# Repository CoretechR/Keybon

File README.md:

# Keybon - Adaptive Macro Keyboard

Keybon is a macro keyboard with configurable layouts and functions. Integrated into each of its nine tactile buttons is a 0.66” OLED screen. Depending on which app is active on the connected computer, Keybon switches to the suitable key layout thanks to its companion software.

# Instructions

1.  Download the USB bootloader: https://github.com/rogerclarkmelbourne/STM32duino-bootloader

    Connect a USB-to-Serial adapter to the TX/RX pins of your board. Close the BOOT0 jumper before applying power.
    
    Flash the USB bootloader to the STM32 via the STM32 flasher:  https://www.st.com/en/development-tools/flasher-stm32.html
2.  Install the required Arduino libraries listed in the keybon.ino file

    Important: Adafruit_GFX_Library version 1.7.5 must be installed (dependencies for newer versions are incompatible with the STM32)
    
    Add the following lines to the Adafruit_SSD1306 library (in Arduino\libraries\Adafruit_SSD1306\Adafruit_SSD1306.cpp) 
    
    ```C++
    else if ((WIDTH == 128) && (HEIGHT == 48)) {
    comPins = 0x12;
	  contrast = (vccstate == SSD1306_EXTERNALVCC) ? 0x9F : 0xCF;
    }
    ```
3.  Install STM32 support for the Arduino IDE: https://github.com/rogerclarkmelbourne/Arduino_STM32

    Install the corresponding drivers: https://github.com/rogerclarkmelbourne/Arduino_STM32/tree/master/drivers
4.  Compile and upload the Arduino sketch:

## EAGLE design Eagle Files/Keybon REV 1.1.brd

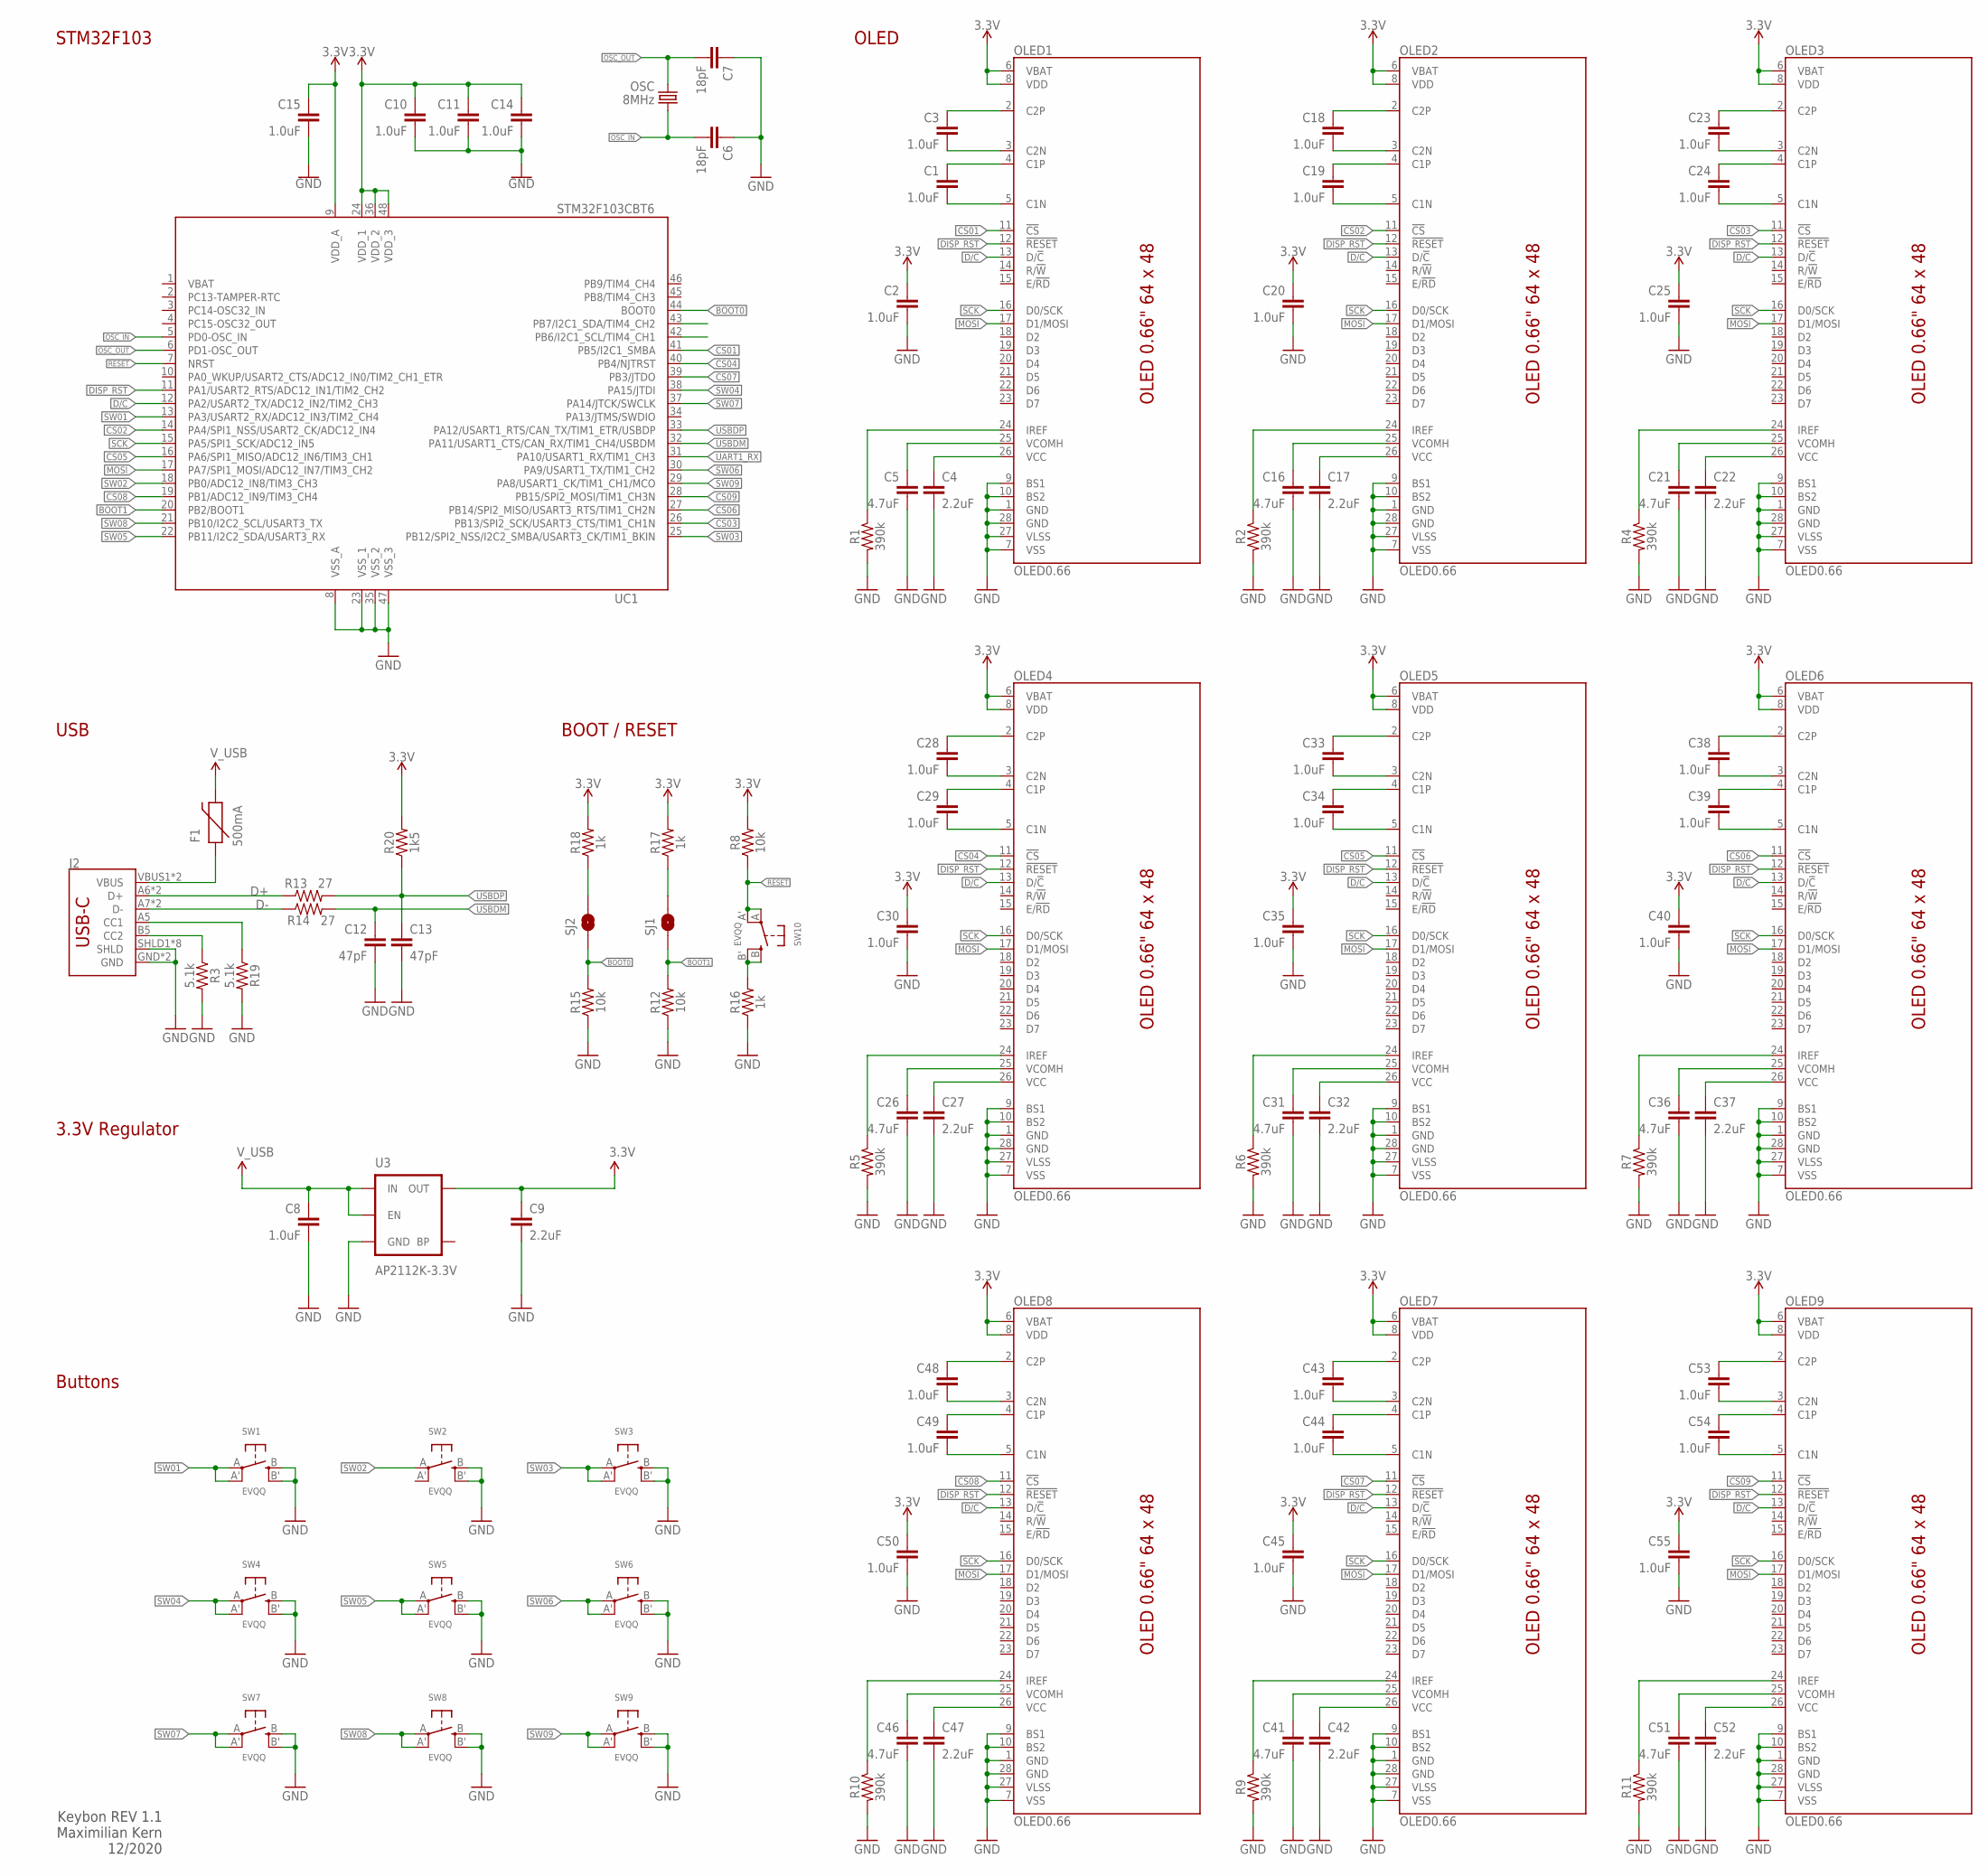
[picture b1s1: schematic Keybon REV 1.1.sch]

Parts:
C1, C2, C3, C8, C10, C11, C14, C15, C18, C19, C20, C23, C24, C25, C28, C29, C30, C33, C34, C35, C38, C39, C40, C43, C44, C45, C48, C49, C50, C53, C54, C55: 1.0uF; 0805
C4, C9, C17, C22, C27, C32, C37, C42, C47, C52: 2.2uF; 0805
C5, C16, C21, C26, C31, C36, C41, C46, C51: 4.7uF; 0603
C6, C7: 18pF; 0603
C12, C13: 47pF; 0603
F1: 500mA; PTC-1206
J2: USB_C16PIN; USB-C-16P
OLED1, OLED2, OLED3, OLED4, OLED5, OLED6, OLED7, OLED8, OLED9: OLED0.66; OLED-0.66-64X48
OSC: 8MHz; CRYSTAL-SMD-5X3
R1, R2, R4, R5, R6, R7, R9, R10, R11: 390k; 0603
R3, R19: 5.1k; 0603
R8, R12, R15: 10k; 0603
R13, R14: 27; 0603
R16, R17, R18: 1k; 0603
R20: 1k5; 0603
SJ1, SJ2: JUMPER-PAD-2-NOYES_SILK; PAD-JUMPER-2-NO_YES_SILK
SW1, SW2, SW3, SW4, SW5, SW6, SW7, SW8, SW9, SW10: EVQQ; EVQ-Q2_SMALLER
U3: AP2112K-3.3V; SOT23-5
UC1: STM32F103CBT6; LQFP48

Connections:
3.3V: C2.1, C9.1, C10.1, C11.1, C14.1, C15.1, C20.1, C25.1, C30.1, C35.1, C40.1, C45.1, C50.1, C55.1, OLED1.6 (VBAT), OLED1.8 (VDD), OLED2.6 (VBAT), OLED2.8 (VDD), OLED3.6 (VBAT), OLED3.8 (VDD), OLED4.6 (VBAT), OLED4.8 (VDD), OLED5.6 (VBAT), OLED5.8 (VDD), OLED6.6 (VBAT), OLED6.8 (VDD), OLED7.6 (VBAT), OLED7.8 (VDD), OLED8.6 (VBAT), OLED8.8 (VDD), OLED9.6 (VBAT), OLED9.8 (VDD), R8.2, R17.2, R18.2, R20.2, U3.5 (OUT), UC1.9 (VDD_A), UC1.24 (VDD_1), UC1.36 (VDD_2), UC1.48 (VDD_3)
BOOT0: R15.2, SJ2.1, UC1.44 (BOOT0)
BOOT1: R12.2, SJ1.1, UC1.20 (PB2/BOOT1)
C1N: C1.2, OLED1.5 (C1N)
C1N1: C19.2, OLED2.5 (C1N)
C1N2: C24.2, OLED3.5 (C1N)
C1N3: C29.2, OLED4.5 (C1N)
C1N4: C34.2, OLED5.5 (C1N)
C1N5: C39.2, OLED6.5 (C1N)
C1N6: C44.2, OLED7.5 (C1N)
C1N7: C49.2, OLED8.5 (C1N)
C1N8: C54.2, OLED9.5 (C1N)
C1P: C1.1, OLED1.4 (C1P)
C1P1: C19.1, OLED2.4 (C1P)
C1P2: C24.1, OLED3.4 (C1P)
C1P3: C29.1, OLED4.4 (C1P)
C1P4: C34.1, OLED5.4 (C1P)
C1P5: C39.1, OLED6.4 (C1P)
C1P6: C44.1, OLED7.4 (C1P)
C1P7: C49.1, OLED8.4 (C1P)
C1P8: C54.1, OLED9.4 (C1P)
C2N: C3.2, OLED1.3 (C2N)
C2N1: C18.2, OLED2.3 (C2N)
C2N2: C23.2, OLED3.3 (C2N)
C2N3: C28.2, OLED4.3 (C2N)
C2N4: C33.2, OLED5.3 (C2N)
C2N5: C38.2, OLED6.3 (C2N)
C2N6: C43.2, OLED7.3 (C2N)
C2N7: C48.2, OLED8.3 (C2N)
C2N8: C53.2, OLED9.3 (C2N)
C2P: C3.1, OLED1.2 (C2P)
C2P1: C18.1, OLED2.2 (C2P)
C2P2: C23.1, OLED3.2 (C2P)
C2P3: C28.1, OLED4.2 (C2P)
C2P4: C33.1, OLED5.2 (C2P)
C2P5: C38.1, OLED6.2 (C2P)
C2P6: C43.1, OLED7.2 (C2P)
C2P7: C48.1, OLED8.2 (C2P)
C2P8: C53.1, OLED9.2 (C2P)
CS01: OLED1.11 (!CS!), UC1.41 (PB5/I2C1_SMBA)
CS02: OLED2.11 (!CS!), UC1.14 (PA4/SPI1_NSS/USART2_CK/ADC12_IN4)
CS03: OLED3.11 (!CS!), UC1.26 (PB13/SPI2_SCK/USART3_CTS/TIM1_CH1N)
CS04: OLED4.11 (!CS!), UC1.40 (PB4/NJTRST)
CS05: OLED5.11 (!CS!), UC1.16 (PA6/SPI1_MISO/ADC12_IN6/TIM3_CH1)
CS06: OLED6.11 (!CS!), UC1.27 (PB14/SPI2_MISO/USART3_RTS/TIM1_CH2N)
CS07: OLED7.11 (!CS!), UC1.39 (PB3/JTDO)
CS08: OLED8.11 (!CS!), UC1.19 (PB1/ADC12_IN9/TIM3_CH4)
CS09: OLED9.11 (!CS!), UC1.28 (PB15/SPI2_MOSI/TIM1_CH3N)
D+: J2.A6 (D+), J2.B6 (D+), R13.1
D-: J2.A7 (D-), J2.B7 (D-), R14.1
D/C: OLED1.13 (D/!C!), OLED2.13 (D/!C!), OLED3.13 (D/!C!), OLED4.13 (D/!C!), OLED5.13 (D/!C!), OLED6.13 (D/!C!), OLED7.13 (D/!C!), OLED8.13 (D/!C!), OLED9.13 (D/!C!), UC1.12 (PA2/USART2_TX/ADC12_IN2/TIM2_CH3)
DISP_RST: OLED1.12 (!RESET!), OLED2.12 (!RESET!), OLED3.12 (!RESET!), OLED4.12 (!RESET!), OLED5.12 (!RESET!), OLED6.12 (!RESET!), OLED7.12 (!RESET!), OLED8.12 (!RESET!), OLED9.12 (!RESET!), UC1.11 (PA1/USART2_RTS/ADC12_IN1/TIM2_CH2)
GND: C2.2, C4.2, C5.2, C6.1, C7.1, C8.2, C9.2, C10.2, C11.2, C12.2, C13.2, C14.2, C15.2, C16.2, C17.2, C20.2, C21.2, C22.2, C25.2, C26.2, C27.2, C30.2, C31.2, C32.2, C35.2, C36.2, C37.2, C40.2, C41.2, C42.2, C45.2, C46.2, C47.2, C50.2, C51.2, C52.2, C55.2, J2.GND, J2.GND2 (GND), J2.SHLD1 (SHLD), J2.SHLD2 (SHLD), J2.SHLD3 (SHLD), J2.SHLD4 (SHLD), J2.SHLD5 (SHLD), J2.SHLD6 (SHLD), J2.SHLD7 (SHLD), J2.SHLD8 (SHLD), OLED1.1 (GND), OLED1.7 (VSS), OLED1.9 (BS1), OLED1.10 (BS2), OLED1.27 (VLSS), OLED1.28 (GND), OLED2.1 (GND), OLED2.7 (VSS), OLED2.9 (BS1), OLED2.10 (BS2), OLED2.27 (VLSS), OLED2.28 (GND), OLED3.1 (GND), OLED3.7 (VSS), OLED3.9 (BS1), OLED3.10 (BS2), OLED3.27 (VLSS), OLED3.28 (GND), OLED4.1 (GND), OLED4.7 (VSS), OLED4.9 (BS1), OLED4.10 (BS2), OLED4.27 (VLSS), OLED4.28 (GND), OLED5.1 (GND), OLED5.7 (VSS), OLED5.9 (BS1), OLED5.10 (BS2), OLED5.27 (VLSS), OLED5.28 (GND), OLED6.1 (GND), OLED6.7 (VSS), OLED6.9 (BS1), OLED6.10 (BS2), OLED6.27 (VLSS), OLED6.28 (GND), OLED7.1 (GND), OLED7.7 (VSS), OLED7.9 (BS1), OLED7.10 (BS2), OLED7.27 (VLSS), OLED7.28 (GND), OLED8.1 (GND), OLED8.7 (VSS), OLED8.9 (BS1), OLED8.10 (BS2), OLED8.27 (VLSS), OLED8.28 (GND), OLED9.1 (GND), OLED9.7 (VSS), OLED9.9 (BS1), OLED9.10 (BS2), OLED9.27 (VLSS), OLED9.28 (GND), R1.2, R2.2, R3.2, R4.2, R5.2, R6.2, R7.2, R9.2, R10.2, R11.2, R12.1, R15.1, R16.1, R19.2, SW1.B (S), SW1.B' (S1), SW2.B (S), SW2.B' (S1), SW3.B (S), SW3.B' (S1), SW4.B (S), SW4.B' (S1), SW5.B (S), SW5.B' (S1), SW6.B (S), SW6.B' (S1), SW7.B (S), SW7.B' (S1), SW8.B (S), SW8.B' (S1), SW9.B (S), SW9.B' (S1), U3.2 (GND), UC1.8 (VSS_A), UC1.23 (VSS_1), UC1.35 (VSS_2), UC1.47 (VSS_3)
IREF: OLED1.24 (IREF), R1.1
IREF1: OLED2.24 (IREF), R2.1
IREF2: OLED3.24 (IREF), R4.1
IREF3: OLED4.24 (IREF), R5.1
IREF4: OLED5.24 (IREF), R6.1
IREF5: OLED6.24 (IREF), R7.1
IREF6: OLED7.24 (IREF), R9.1
IREF7: OLED8.24 (IREF), R10.1
IREF8: OLED9.24 (IREF), R11.1
MOSI: OLED1.17 (D1/MOSI), OLED2.17 (D1/MOSI), OLED3.17 (D1/MOSI), OLED4.17 (D1/MOSI), OLED5.17 (D1/MOSI), OLED6.17 (D1/MOSI), OLED7.17 (D1/MOSI), OLED8.17 (D1/MOSI), OLED9.17 (D1/MOSI), UC1.17 (PA7/SPI1_MOSI/ADC12_IN7/TIM3_CH2)
unnamed: R16.2, SW10.B (S), SW10.B' (S1)
unnamed: R18.1, SJ2.2
unnamed: R17.1, SJ1.2
unnamed: C4.1, OLED1.26 (VCC)
unnamed: C17.1, OLED2.26 (VCC)
unnamed: C22.1, OLED3.26 (VCC)
unnamed: C37.1, OLED6.26 (VCC)
unnamed: C32.1, OLED5.26 (VCC)
unnamed: J2.A5 (CC1), R19.1
unnamed: C27.1, OLED4.26 (VCC)
unnamed: J2.B5 (CC2), R3.1
unnamed: C47.1, OLED8.26 (VCC)
unnamed: C42.1, OLED7.26 (VCC)
unnamed: C52.1, OLED9.26 (VCC)
OSC_IN: C6.2, OSC.1, UC1.5 (PD0-OSC_IN)
OSC_OUT: C7.2, OSC.3 (2), UC1.6 (PD1-OSC_OUT)
RESET: R8.1, SW10.A, SW10.A' (P1), UC1.7 (NRST)
SCK: OLED1.16 (D0/SCK), OLED2.16 (D0/SCK), OLED3.16 (D0/SCK), OLED4.16 (D0/SCK), OLED5.16 (D0/SCK), OLED6.16 (D0/SCK), OLED7.16 (D0/SCK), OLED8.16 (D0/SCK), OLED9.16 (D0/SCK), UC1.15 (PA5/SPI1_SCK/ADC12_IN5)
SW01: SW1.A, SW1.A' (P1), UC1.13 (PA3/USART2_RX/ADC12_IN3/TIM2_CH4)
SW02: SW2.A, UC1.18 (PB0/ADC12_IN8/TIM3_CH3)
SW03: SW3.A, SW3.A' (P1), UC1.25 (PB12/SPI2_NSS/I2C2_SMBA/USART3_CK/TIM1_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)
SW04: SW4.A, SW4.A' (P1), UC1.38 (PA15/JTDI)
SW05: SW5.A, SW5.A' (P1), UC1.22 (PB11/I2C2_SDA/USART3_RX)
SW06: SW6.A, SW6.A' (P1), UC1.30 (PA9/USART1_TX/TIM1_CH2)
SW07: SW7.A, SW7.A' (P1), UC1.37 (PA14/JTCK/SWCLK)
SW08: SW8.A, SW8.A' (P1), UC1.21 (PB10/I2C2_SCL/USART3_TX)
SW09: SW9.A, SW9.A' (P1), UC1.29 (PA8/USART1_CK/TIM1_CH1/MCO)
UART1_RX: UC1.31 (PA10/USART1_RX/TIM1_CH3)
USBDM: C12.1, R14.2, UC1.32 (PA11/USART1_CTS/CAN_RX/TIM1_CH4/USBDM)
USBDP: C13.1, R13.2, R20.1, UC1.33 (PA12/USART1_RTS/CAN_TX/TIM1_ETR/USBDP)
VBAT: UC1.1 (VBAT)
VCOMH: C5.1, OLED1.25 (VCOMH)
VCOMH1: C16.1, OLED2.25 (VCOMH)
VCOMH2: C21.1, OLED3.25 (VCOMH)
VCOMH3: C26.1, OLED4.25 (VCOMH)
VCOMH4: C31.1, OLED5.25 (VCOMH)
VCOMH5: C36.1, OLED6.25 (VCOMH)
VCOMH6: C41.1, OLED7.25 (VCOMH)
VCOMH7: C46.1, OLED8.25 (VCOMH)
VCOMH8: C51.1, OLED9.25 (VCOMH)
VUSB-RAW: F1.1, J2.VBUS1 (VBUS), J2.VBUS2 (VBUS)
V_USB: C8.1, F1.2, U3.1 (IN), U3.3 (EN)

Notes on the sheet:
Buttons
OLED
STM32F103
USB
BOOT / RESET
3.3V Regulator
Keybon REV 1.1 Maximilian Kern 12/2020

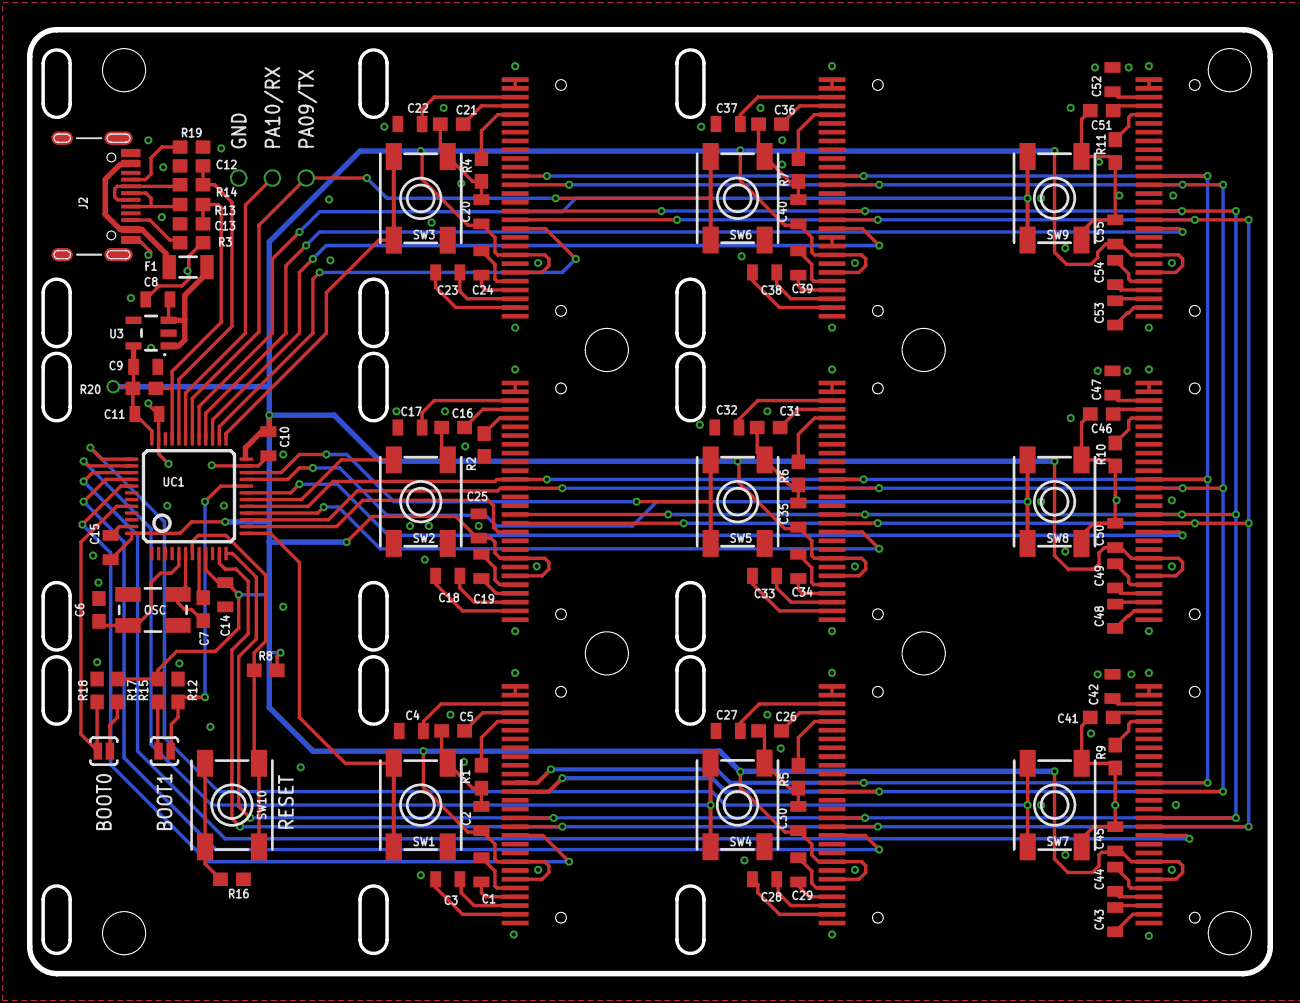
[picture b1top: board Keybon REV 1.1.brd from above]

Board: 2 copper layers, 92.0 x 70.0 mm, 101 parts (0 on the bottom side), 103 nets.

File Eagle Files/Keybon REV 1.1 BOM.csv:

Qty,Value,Device,Package,Parts,LCSC Link
1,,USB_C16PIN,USB-C-16P,J2,https://lcsc.com/product-detail/USB-Connectors_SOFNG-MC-311D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
32,1.0uF,,0603,C1; C2; C3; C8; C10; C11; C14; C15; C18; C19; C20; C23; C24; C25; C28; C29; C30; C33; C34; C35; C38; C39; C40; C43; C44; C45; C48; C49; C50; C53; C54; C55,https://lcsc.com/product-detail/Multilayer-Ceramic-Capacitor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
3,10k,,0603,R8; R12; R15,https://lcsc.com/product-detail/Chip-Resistor-Surface-Mount_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
2,18pF,,0603,C6; C7,https://lcsc.com/product-detail/Multilayer-Ceramic-Capacitor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
3,1k,,0603,R16; R17; R18,https://lcsc.com/product-detail/Chip-Resistor-Surface-Mount_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
1,1k5,,0603,R20,https://lcsc.com/product-detail/Chip-Resistor-Surface-Mount_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
10,2.2uF,,0603,C4; C9; C17; C22; C27; C32; C37; C42; C47; C52,https://lcsc.com/product-detail/Multilayer-Ceramic-Capacitor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
2,27,,0603,R13; R14,https://lcsc.com/product-detail/Chip-Resistor-Surface-Mount_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
9,390k,,0603,R1; R2; R4; R5; R6; R7; R9; R10; R11,https://lcsc.com/product-detail/Chip-Resistor-Surface-Mount_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
9,4.7uF,,0603,C5; C16; C21; C26; C31; C36; C41; C46; C51,https://lcsc.com/product-detail/Multilayer-Ceramic-Capacitor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
2,47pF,,0603,C12; C13,https://lcsc.com/product-detail/Multilayer-Ceramic-Capacitor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
2,5.1k,,0603,R3; R19,https://lcsc.com/product-detail/Chip-Resistor-Surface-Mount_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
1,500mA,PTCSMD,PTC-1206,F1,https://lcsc.com/product-detail/PTC-Resettable-Fuses_Fuzetec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
1,8MHz,CRYSTAL5X3,CRYSTAL-SMD-5X3,OSC,https://lcsc.com/product-detail/SMD-Crystal-Resonators_Abrac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
1,AP2112K-3.3V,V_REG_LDOSMD,SOT23-5,U3,https://lcsc.com/product-detail/Dropout-Regulators-LDO_Diode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
10,EVQQ,B3FS-1000P,EVQ-Q2_SMALLER,SW1; SW2; SW3; SW4; SW5; SW6; SW7; SW8; SW9; SW10,https://lcsc.com/product-detail/Tactile-Switches_Omron-Elect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
9,OLED0.66,OLED0.66,OLED-0.66-64X48,OLED1; OLED2; OLED3; OLED4; OLED5; OLED6; OLED7; OLED8; OLED9,https://lcsc.com/product-detail/OLED-Displays-Modules_UG-Uni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
1,STM32F103C8T6,STM32F103C8T6,LQFP48,UC1,https://lcsc.com/product-detail/ST-Microelectronics_STMicroe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

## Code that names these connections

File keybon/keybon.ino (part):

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
#define PRODUCT_ID 0x29

#define SW01 PA3
#define SW02 PB0
#define SW03 PB12
#define SW04 PA15
#define SW05 PB11
#define SW06 PA9
#define SW07 PA14
#define SW08 PB10
#define SW09 PA8

#define OLED_MOSI  PA7
#define OLED_CLK   PA5
#define OLED_DC    PA2
#define OLED_CS01    PB5
#define OLED_CS02    PA4
#define OLED_CS03    PB13
#define OLED_CS04    PB4
#define OLED_CS05    PA6
#define OLED_CS06    PB14
#define OLED_CS07    PB3
#define OLED_CS08    PB1
#define OLED_CS09    PB15
#define OLED_RESET PA1

Adafruit_SSD1306 OLED01(128, 48, OLED_MOSI, OLED_CLK, OLED_DC, OLED_RESET, OLED_CS01);
Adafruit_SSD1306 OLED02(128, 48, OLED_MOSI, OLED_CLK, OLED_DC, OLED_RESET, OLED_CS02);
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
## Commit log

2020-12-05 Quicker Layout Switching
    Replaced GetPixel so Layout icons load much faster
2020-12-18 BOM added
2021-02-09 bad silkscreen placement fixed
2021-02-09 instructions added
2021-03-06 Added Fusion360 Source file (fix #3)
2021-03-15 BOOT1 changed to BOOT0 in instructions
    The BOOT0 jumper must be shorted to enter serial boot!
2022-07-14 Gerber RS274X files added
2023-12-17 Compiled binary added
2023-12-17 bitmap examples added

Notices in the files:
parts and their libraries:
SparkFun-Capacitors: Licensing: Creative Commons ShareAlike 4.0 International - https://creativecommons.org/licenses/by-sa/4.0
